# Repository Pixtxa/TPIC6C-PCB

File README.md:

# TPIC6C-PCB

Breakout board for [TPIC6C596 shift registers with 8x open drain output](https://www.ti.com/product/TPIC6C596) with neopixels as status leds.

## Features
* Daisy chaining of multiple boards
  * [nyanyanyanyanyanyanya](https://knowyourmeme.com/memes/nyanyanyanyanyanyanya)
  * "ONE WAY" marks represent the direction, where data goes in and where it comes out
* Neopixel LEDs (WS2812, WS2812B, SK6812 or whatever) 
  * Not needed, but nice to have
  * Work independent from the shift registers; only share the same voltage
  * Can be used as output status leds (2x RGBW = 8 bit) or whatever the software wants them to do
  * Can function as signal repeaters to connect a [NeoPixel Arcade Button](https://www.thingiverse.com/thing:823588) at the end
  * Even if your project is unfinished, it can have nice rainbow animations in an early state
* Main part
  * IC + Basic components
  * 1 Neopixel LED
  * GND, V+ and all 8 Outputs as 2.54 mm pitch THT connector
  * V+ and 5 Outputs (D0 ... D4) as 1.27 mm pitch SMD connector
  * 23 mm x 40.64 mm
  * Connection-Pitch of 35.56 mm
* Extension part
  * Can be cut away if not needed 
  * 1 Neopixel LED
    * Or solder jumper for connecting the data line without neopixel
  * GND, V+ and 4 Outputs as 2.54 mm pitch THT connector
  * V+ and 4 Outputs (D4 ... D7) as 1.27 mm pitch SMD connector
  * 2.54 mm screw connector for V+
  * Montage hole
  * Extends PCB to 23 mm x 85.08 mm
  * Connection-Pitch of 80 mm
  * Output connectors 40 mm appart of the main part ones, resulting in output pitch of 40 mm when using D0-D3 on main and D4-D7 on extension part
* Side Connectors
  * Double row connectors
    * Better stability
    * Box headers can be used to connect PCBs over longer distance
    * Can be used to variate the pitch a little
    * Half of outer holes can be cut away to have some kind of plated edge connector, but it doesn't really work for a huge amount of PCBs
  * SPI can be used to set the outputs
    * CLK: SCK
    * D_IN: MOSI
    * SS: Latch
  * Pinout
    * nCLEAR/nCLR (optional)
      * LOW = Reset IC
      * R1 as Pull-Up avialable
    * nOE/nG (optional)
      * LOW = Output Enable
      * R2 as Pull-Down avialable
      * Can be used for PWM dimming 
    * Latch/RSCK/SPI_SS
      * Rising Edge: Copy data from shift register to output registers
      * SPI_SS can be used
    * D_IN/SER_IN/SPI_MOSI
      * Data in
      * SPI_MOSI can be used
    * D_OUT/SER_OUT
      * Data out for next shift registers data in
    * CLK/RCK/SPI_SCK
      * Rising Edge: Move data one step forward
      * SPI_SCK can be used
    * 5V/VCC
      * 4.5 ... 5.5 V supply voltage for shift register logic and neopixel
      * Level shifters might be needed for the other input signals
    * GND
      * Ground
    * V+ (optional)
      * 0...33 V
      * Screw terminal can be used for individual V+ on each PCB
      * It's only passed, so it also can be wired external without connecting it to the PCB
    * LED_IN
      * Neopixel Data in
    * LED_OUT
      * Neopixel Data out
* Designed to control (huge amounts of) [WERMA](https://werma.com) signal lamps
  * 24V compatible outputs
  * V+ is X0/COM
  * D0-D7 are outputs for X1, X2, ...
  * GND can be used as always-on output (e. g. for powering a [24V eSIGN](https://www.werma.com/en/s_c1684i7007/65760055.html) or [Transceiver](https://www.werma.com/en/s_c0i6509/86200003.html))
  * Main part SMD connector features 5 Outputs, because KombiSIGN can handle up to 5 Tiers
  * 40 mm output pitch when using up to 4 outputs, because MC35 has 35 mm diameter and 4 inputs, leaving 5 mm space between lamps
  * 80 mm output pitch when using 5 or more outputs, because eSIGN/KS71/KS72 have 70 mm diameter, leaving 10 mm space between lamps

## Known bugs
* Heat transfer
  * Datasheet shows a recommended layout example which isn't in use
  * No problem for me, because I'm far away of these limits
  * Maybe gluing on heatsinks might work
  * Redesign options
    * Implement it
      * Using 4 Layers
      * Increase PCB size
    * Use another IC with better cooling options
    * Add dedicated MOSFETs for higher currents
* Voltage drop on power lines can cause problems on longer chains
  * Voltage drop on V+ only affects the outputs
  * Voltage drop on 5V mostly occurs when using the neopixels on high brightness
  * Voltage drop on GND affects the neopixels and shift registers and is mostly caused by enabled outputs
    * The shift registers glitch if voltage is too low
  * I've ordered the PCBs with only 1 oz Outer Copper Weight
  * I reccomend adding an extra cable for 5V, GND and V+ and connect it regulary
  * Redesign options
    * Add ground plane
    * Increase size of power lines, maybe use both sides of PCB, maybe also increase PCB size to fit everything
    * Order 2 oz Outer Copper Weight
    * Use 4 Layers
    * Pads for connecting cables that run in parallel
    * Use a single box connector for each PCB
      * Most current goes through external ribbon cable
      * Multiple wires for same power lines for less resistance
      * Somehow find an easy way to cut and connect the D_IN/D_OUT and LED_IN/LED_OUT wire correctly
* Missing Resistors/Power-On-Reset
  * Most MCUs have IOs that are inputs on startup and when uploading firmware
  * Open inputs act as antennas
  * Glitches are painful when the outputs are connected to loud buzzers
  * Adding an Pull-Up + IO to nOE helps
  * Redesign options
    * Adding option for Pull-Up on nOE, so outputs are off until the MCU switches this pin to LOW
      * Might cause problems if MCU doesn't run on 5 V and no level shifter is used
      * MCU would need this IO only for start up, if PWM-dimming isn't in use
        * Maybe add solder jumper to latch input; in some cases it's okay to blank all outputs when switching them
    * Adding a simple RC Power-On-Reset to nCLEAR and a Pull-Down to Latch
      * Data in the shift register might glitch, but the controller can fill it with data before latching it to the outputs
      * On power-on, the output registers would be cleared and stay off
      * On firmware upgrades/MCU-reset, the output registers will keep their value
        * Might result in an active buzzer
        * Allows silent/invisible MCU restarts/updates in the background
* Not all WERMA products can operate with V+ as COM
  * I've only had this problem with [LED Perm. Beacon WM 24VDC GN/YE/RD](https://www.werma.com/en/s_c1031i1973/89408055.html)
  * At least this board can drive PNP Transistors + Resistors as HIGH-Side-Switches
  * Redesign options
    * Add pads to V+ to add Pull-Up resistors, so P-Channel-MOSFETs can be used as HIGH-Side switches
      * These resistors could also help if LEDs light up dim because of EMC influences on long lines
      * These pads could also function for adding freewheeling diodes when switching inductive loads

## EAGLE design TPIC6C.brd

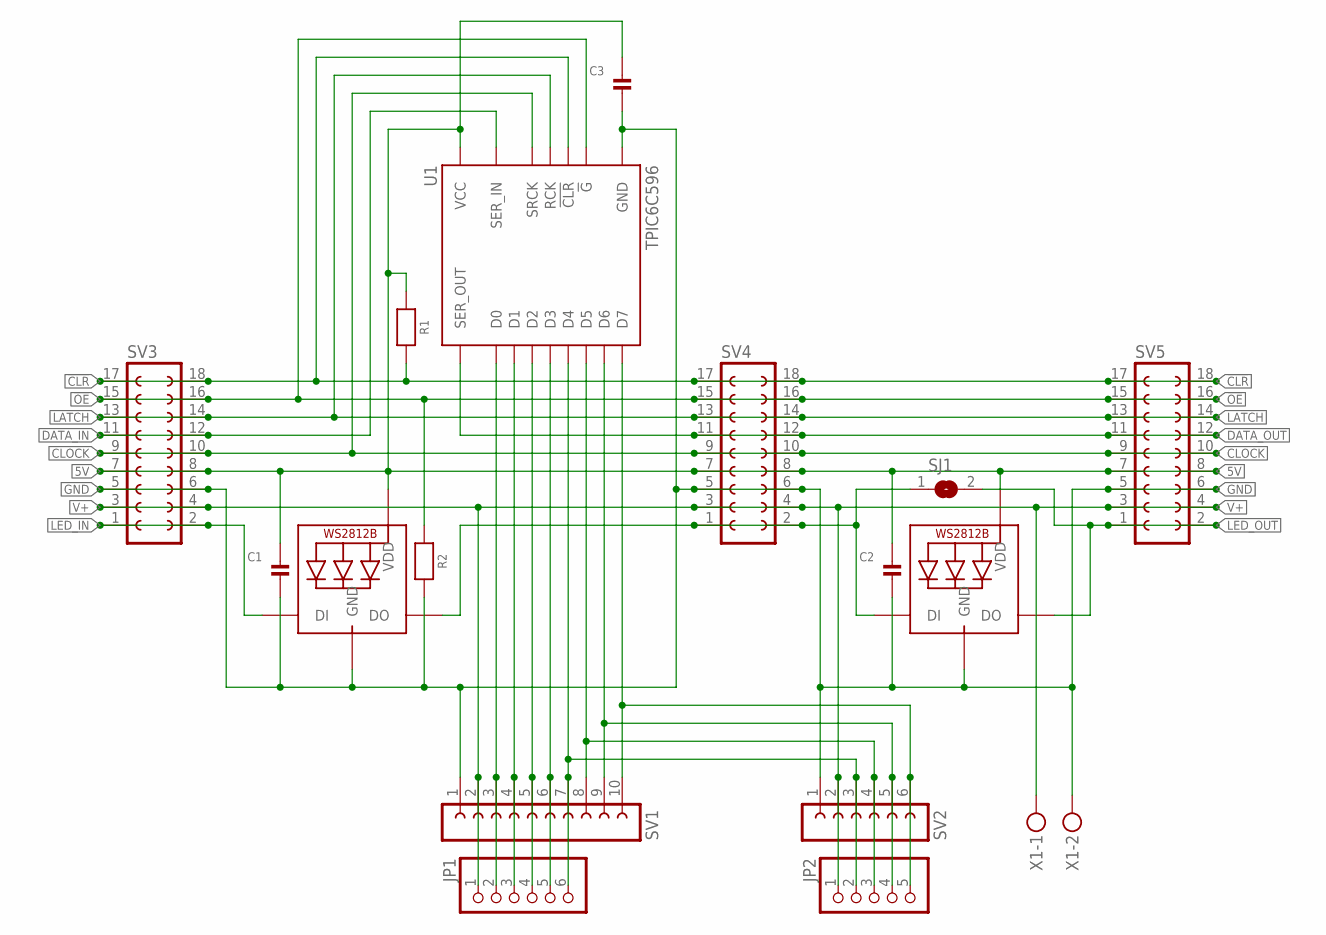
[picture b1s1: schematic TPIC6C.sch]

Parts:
C1, C2, C3: CAP_CERAMIC0603; 0603
JP1: HEADER-1X61X06_1.27MM; 1X06_1.27MM
JP2: HEADER-1X51.27MM; 1X05_1.27MM
LED1, LED2: WS2812B5050; WS2812B
R1, R2: MICROBUILDER_RESISTOR_0603_NOOUT; MICROBUILDER_0603-NO
SJ1: SOLDERJUMPER; SOLDERJUMPER_ARROW_NOPASTE
SV1: FE10-1; FE10
SV2: FE06-1; FE06
SV3, SV4, SV5: FE09-2NOSILK; FE09-2_NOSILK
U1: TPIC6C596; SO16
X1: MKDSN1,5/2-5,08

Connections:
5V: C1.1, C2.1, C3.1, LED1.1-VDD (VDD), LED2.1-VDD (VDD), R1.1, SV3.7, SV3.8, SV4.7, SV4.8, SV5.7, SV5.8, U1.1 (VCC)
!CLR: R1.2, SV3.17, SV3.18, SV4.17, SV4.18, SV5.17, SV5.18, U1.7 (!CLR)
!OE: R2.1, SV3.15, SV3.16, SV4.15, SV4.16, SV5.15, SV5.16, U1.8 (!G)
CLOCK: SV3.9, SV3.10, SV4.9, SV4.10, SV5.9, SV5.10, U1.15 (SRCK)
D0: JP1.2, SV1.3, U1.3 (D0)
D1: JP1.3, SV1.4, U1.4 (D1)
D2: JP1.4, SV1.5, U1.5 (D2)
D3: JP1.5, SV1.6, U1.6 (D3)
D4: JP1.6, JP2.2, SV1.7, SV2.3, U1.11 (D4)
D5: JP2.3, SV1.8, SV2.4, U1.12 (D5)
D6: JP2.4, SV1.9, SV2.5, U1.13 (D6)
D7: JP2.5, SV1.10, SV2.6, U1.14 (D7)
DATA_IN: SV3.11, SV3.12, U1.2 (SER_IN)
DATA_OUT: SV4.11, SV4.12, SV5.11, SV5.12, U1.9 (SER_OUT)
GND: C1.2, C2.2, C3.2, LED1.3-GND (GND), LED2.3-GND (GND), R2.2, SV1.1, SV2.1, SV3.5, SV3.6, SV4.5, SV4.6, SV5.5, SV5.6, U1.16 (GND), X1.2
LATCH: SV3.13, SV3.14, SV4.13, SV4.14, SV5.13, SV5.14, U1.10 (RCK)
LED_IN: LED1.4-DIN (DI), SV3.1, SV3.2
LED_OUT: LED2.2-DOUT (DO), SJ1.2, SV5.1, SV5.2
LED_OUT_IN: LED1.2-DOUT (DO), LED2.4-DIN (DI), SJ1.1, SV4.1, SV4.2
V+: JP1.1, JP2.1, SV1.2, SV2.2, SV3.3, SV3.4, SV4.3, SV4.4, SV5.3, SV5.4, X1.1

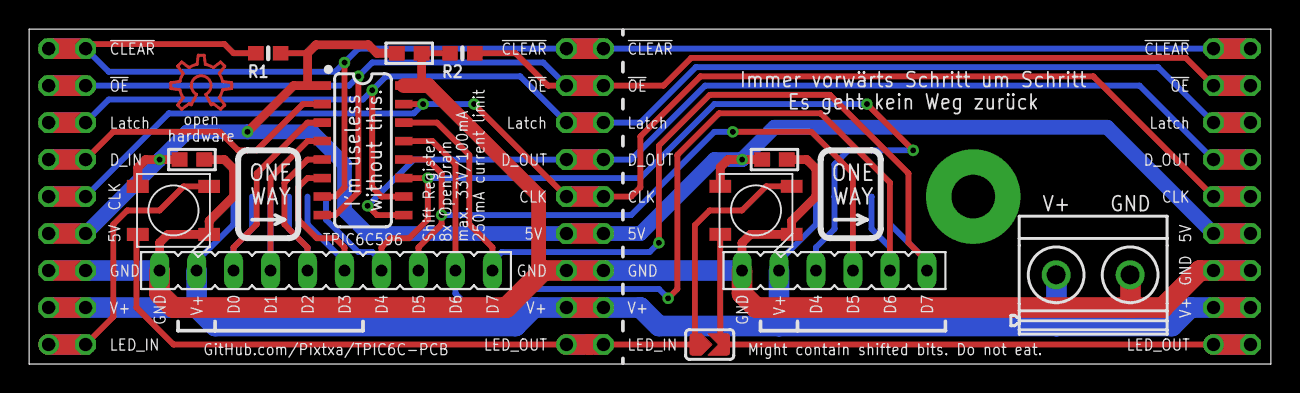
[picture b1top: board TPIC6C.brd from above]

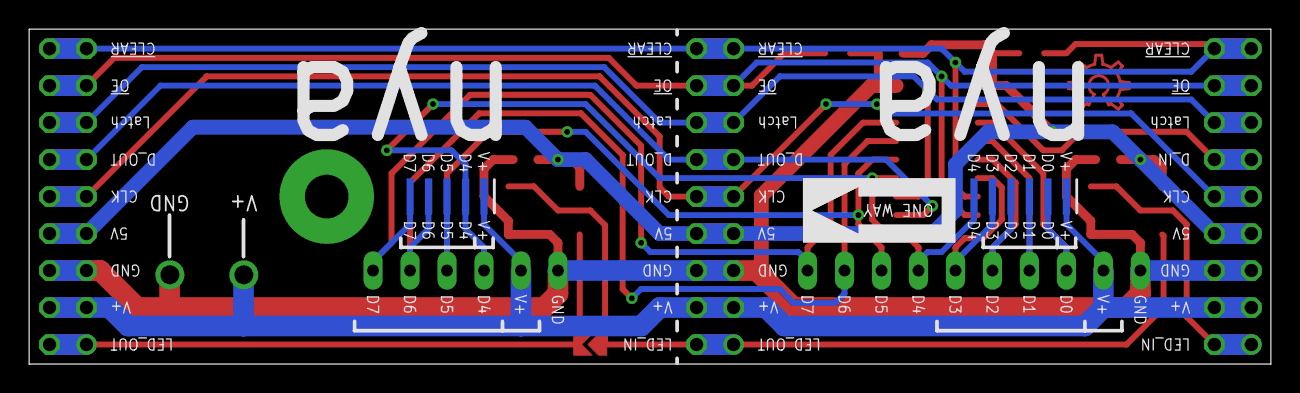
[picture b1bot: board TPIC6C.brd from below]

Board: 2 copper layers, 85.3 x 23.0 mm, 17 parts (2 on the bottom side), 20 nets.

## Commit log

2023-11-29 Create LICENSE
2023-11-30 Added PCB design files
2023-11-30 Update README.md
    Added detail picture of PCB

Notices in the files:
parts and their libraries:
SparkFun-IC-Logic: Licensing: Creative Commons ShareAlike 4.0 International - https://creativecommons.org/licenses/by-sa/4.0
microbuilder: This work is placed in the public domain, and may be freely used for commercial and non-commercial work with the following conditions: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
